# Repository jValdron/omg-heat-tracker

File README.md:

# omg-heat-tracker
## Purpose
The purpose of this project is to provide our local [flyball](https://www.flyball.org) club with a heat tracker. The heat tracker is used to keep track of which heat we are currently on during a flyball race. A race is usually a best 3 out of 5 heats, or a 4 out of 4 heats. This keeps track of which team won which heats.

## Notice
The following is provided without support. Use it at your own will/risk.

## Design
The heat tracker is simply composed of 5 lights, in a wooden box and looks something like this: 

It is built using relatively cheap components. A custom PCB, _detachable-esp8266-4x-wire-to-board_, provides a somewhat better way to connect a development ESP8266 board, in this case a _LOLIN (WEMOS) D1 R2_, to a few lights (in this case 5 x 7 LEDs controlled by a WS2812B), with a DC power jack.

## API
A REST API is provided by the ESP8266 which exposes endpoints used by the browser based remote. The current endpoints are as follow:

### Remote
The root endpoint, `/`, provides the browser based remote that makes calls to the other endpoints

### Retrieve all heats
Retrieves a list of all of the heats and their results. It will always return _TOTAL_HEATS_ elements.

* **URL:** /heats
* **Method:** `GET`
* **Success Response:**
    * **Code:** 200 <br />
      **Content:** `[ 'left', 'right', 'tie', 'none', 'none ]`
    * **Code:** 200 <br />
      **Content:** `[ 'left', 'left', 'right', 'left', 'none ]`
     * **Code:** 200 <br />
      **Content:** `[ 'none', 'none', 'none', 'none', 'none ]`
* **Sample Call:**
    ```bash
    curl -H "Accept: application/json" -i http://192.168.4.1/heats
    ```

### Set current heat results
Sets the results for the current heat.

* **URL:** /heat
* **Method:** `POST`
* **Data Params**
    This method takes in JSON, with only one property: _result_

    ```json
        {
            "result": "left"
        }
    ```

    The valid values for _result_ are: `left, right, tie`
* **Success Response:**
    * **Code:** 201
* **Error Response:**
  * **Code:** 400 <br />
    **Content:** `{ "error": "Invalid JSON body." }`
* **Sample Call:**
    ```bash
    curl -d '{"result": "right"}' -H "Content-Type: application/json" -X POST http://192.168.4.1/heat
    ```

### Reset race
Resets all heats, starts a new race.

* **URL:** /heats
* **Method:** `DELETE`
* **Success Response:**
    * **Code:** 200
* **Sample Call:**
    ```bash
    curl -H "Content-Type: application/json" -X DELETE http://192.168.4.1/heats
    ```

### Reset last heat
Resets the last heat, in case it was done by mistake.

* **URL:** /heat/last
* **Method:** `DELETE`
* **Success Response:**
    * **Code:** 200
* **Error Response:**
  * **Code:** 400 <br />
    **Content:** `{ "error": "Cannot undo heat, currently on first heat." }`
* **Sample Call:**
    ```bash
    curl -H "Content-Type: application/json" -X DELETE http://192.168.4.1/heat/last
    ```

## OmgHeatTracker.ino
This provides the Arduino compatible code to control the lights. It provides the application logic in order to set the lights according to the heats' results, and provides a way to restart the race. Currently, this is meant to be controlled with a browser, by connecting to an access point broadcasted by the ESP8266. The IP address of the ESP8266 defaults to _192.168.0.1_.

## detachable-esp8266-4x-wire-to-board
Optionally, one can use this PCB (done in EAGLE) in order to facilitate how the LEDs are connected to the LOLIN D1 R2. This provides a PCB that has the _LOLIN D1 R2_ on headers, 5 x board connectors and a DC power jack. It makes it easy to swap the _LOLIN D1 R2_ and the lights.

## TODO
* Add programs, ie: best 3 out of 5, 4 out of 4, etc.

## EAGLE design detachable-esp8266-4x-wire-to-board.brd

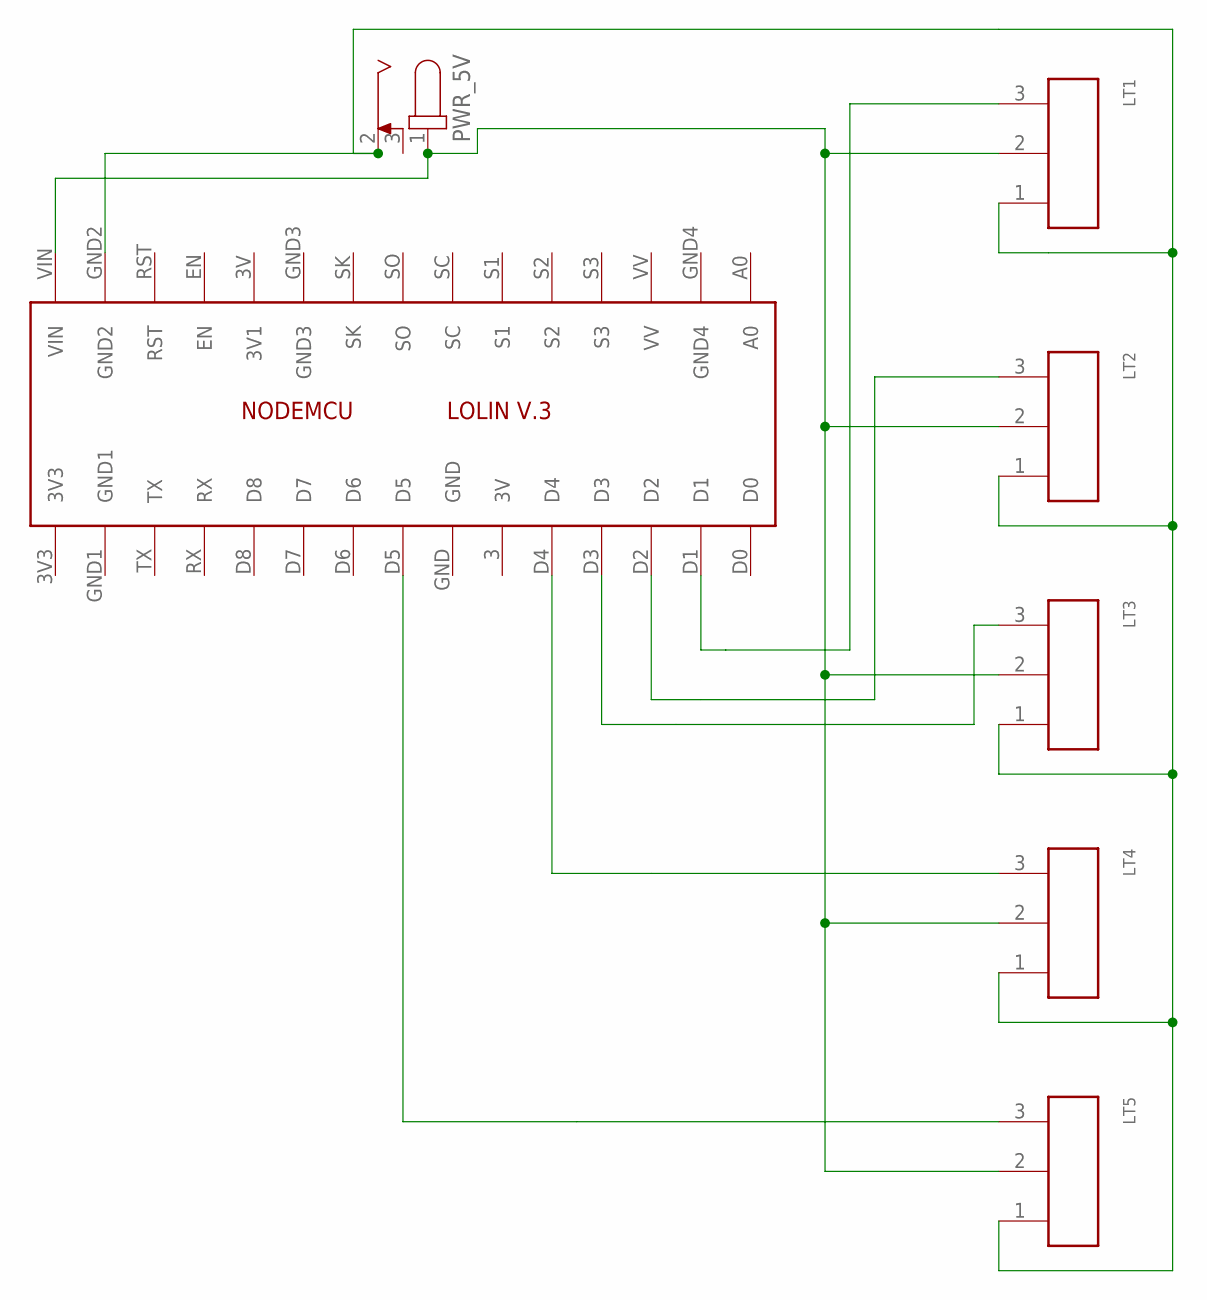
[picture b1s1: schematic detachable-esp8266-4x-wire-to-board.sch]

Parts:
IC1: LOLINV3SMALL; LOLINV3_SMALL
LT1, LT2, LT3, LT4, LT5: 61900311121
PWR_5V: 694103303002; 69410X303002

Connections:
5V: IC1.VIN, LT1.2, LT2.2, LT3.2, LT4.2, LT5.2, PWR_5V.1
GND: IC1.GND2, LT1.1, LT2.1, LT3.1, LT4.1, LT5.1, PWR_5V.2
LT1: IC1.D1, LT1.3
LT2: IC1.D2, LT2.3
LT3: IC1.D3, LT3.3
LT4: IC1.D4, LT4.3
LT5: IC1.D5, LT5.3

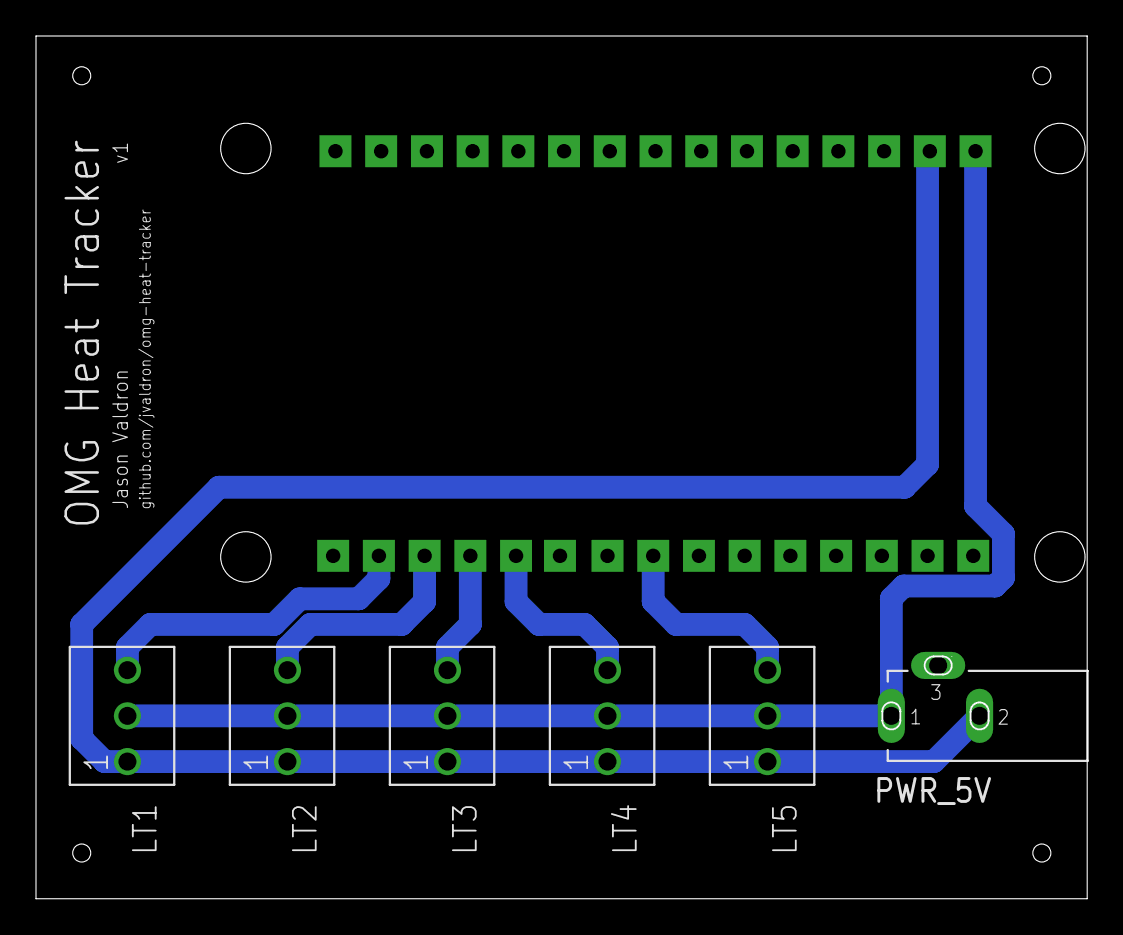
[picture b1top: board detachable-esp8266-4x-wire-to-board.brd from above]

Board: 2 copper layers, 58.3 x 47.8 mm, 7 parts (1 on the bottom side), 7 nets.

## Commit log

2022-05-21 Improve interface
2022-05-21 Fix spinner

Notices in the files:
parts and their libraries:
Wurth_Elektronik_Electromechanic_DC_Powe: Copyright: Würth Elektronik
